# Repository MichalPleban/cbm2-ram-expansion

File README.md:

# CBM-II RAM expansion board

## Warning!

This project is obsolete. For a new hardware project, combining the 8088 card, memory expansion and other hardware features, see the repository at:

https://github.com/MichalPleban/cbm2-8088-ram-board

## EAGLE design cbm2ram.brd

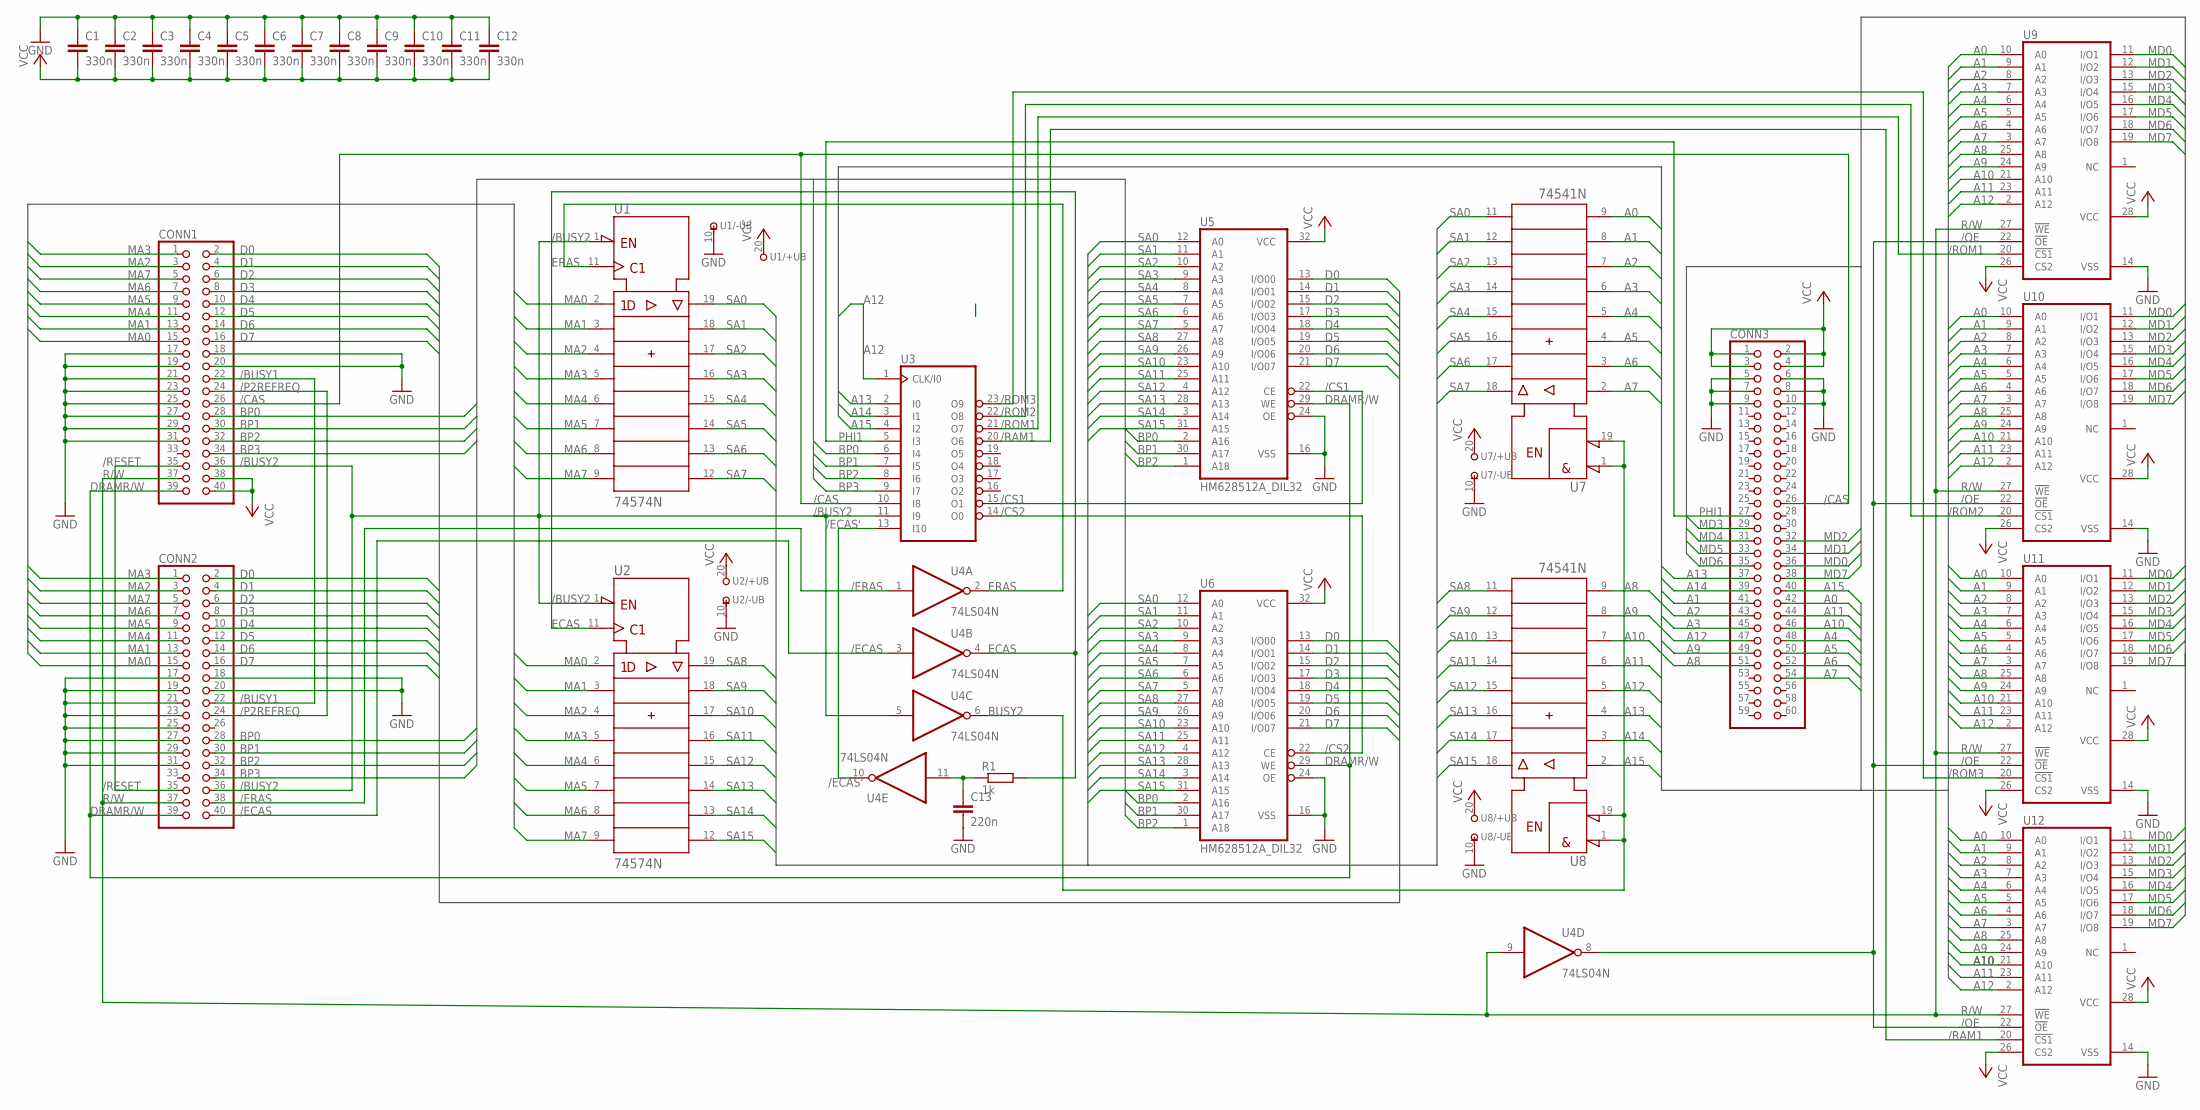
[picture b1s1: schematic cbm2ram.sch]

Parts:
C1, C2, C3, C4, C5, C6, C7, C8, C9, C10, C11, C12: 330n; C5B3
C13: 220n; C5B3
CONN1, CONN2: PINHD-2X20; 2X20
CONN3: PINHD-2X30; 2X30
R1: 1k; 0207/10
U1, U2: 74574N; DIL20
U3: 22V10; DIL24-3
U4: 74LS04N; DIL14
U5, U6: HM628512A_DIL32; DIL32
U7, U8: 74541N; DIL20
U9, U10, U11, U12: 6264A; DIL28-6

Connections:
/BUSY1: CONN1.22, CONN2.22
/BUSY2: CONN1.36, CONN2.36, U1.1 (!OC), U2.1 (!OC), U3.11 (I9), U4.5 (I)
/CAS: CONN1.26, CONN3.26, U3.10 (I8)
/CS1: U3.15 (O1), U5.22 (CE)
/CS2: U3.14 (O0), U6.22 (CE)
/ECAS: CONN2.40, U4.3 (I)
/ECAS': U3.13 (I10), U4.10 (O)
/ERAS: CONN2.38, U4.1 (I)
/OE: U4.8 (O), U9.22 (!OE), U10.22 (!OE), U11.22 (!OE), U12.22 (!OE)
/P2REFREQ: CONN1.24, CONN2.24
/RAM1: U3.20 (O6), U12.20 (!CS1)
/RESET: CONN1.35, CONN2.35
/ROM1: U3.21 (O7), U9.20 (!CS1)
/ROM2: U3.22 (O8), U10.20 (!CS1)
/ROM3: U3.23 (O9), U11.20 (!CS1)
A0: CONN3.42, U7.9 (A8), U9.10 (A0), U10.10 (A0), U11.10 (A0), U12.10 (A0)
A1: CONN3.41, U7.8 (A7), U9.9 (A1), U10.9 (A1), U11.9 (A1), U12.9 (A1)
A2: CONN3.43, U7.7 (A6), U9.8 (A2), U10.8 (A2), U11.8 (A2), U12.8 (A2)
A3: CONN3.45, U7.6 (A5), U9.7 (A3), U10.7 (A3), U11.7 (A3), U12.7 (A3)
A4: CONN3.48, U7.5 (A4), U9.6 (A4), U10.6 (A4), U11.6 (A4), U12.6 (A4)
A5: CONN3.50, U7.4 (A3), U9.5 (A5), U10.5 (A5), U11.5 (A5), U12.5 (A5)
A6: CONN3.52, U7.3 (A2), U9.4 (A6), U10.4 (A6), U11.4 (A6), U12.4 (A6)
A7: CONN3.54, U7.2 (A1), U9.3 (A7), U10.3 (A7), U11.3 (A7), U12.3 (A7)
A8: CONN3.51, U8.9 (A8), U9.25 (A8), U10.25 (A8), U11.25 (A8), U12.25 (A8)
A9: CONN3.49, U8.8 (A7), U9.24 (A9), U10.24 (A9), U11.24 (A9), U12.24 (A9)
A10: CONN3.46, U8.7 (A6), U9.21 (A10), U10.21 (A10), U11.21 (A10), U12.21 (A10)
A11: CONN3.44, U8.6 (A5), U9.23 (A11), U10.23 (A11), U11.23 (A11), U12.23 (A11)
A12: CONN3.47, U3.1 (CLK/I0), U8.5 (A4), U9.2 (A12), U10.2 (A12), U11.2 (A12), U12.2 (A12)
A13: CONN3.37, U3.2 (I0), U8.4 (A3)
A14: CONN3.39, U3.3 (I1), U8.3 (A2)
A15: CONN3.40, U3.4 (I2), U8.2 (A1)
BP0: CONN1.28, CONN2.28, U3.6 (I4), U5.2 (A16), U6.2 (A16)
BP1: CONN1.30, CONN2.30, U3.7 (I5), U5.30 (A17), U6.30 (A17)
BP2: CONN1.32, CONN2.32, U3.8 (I6), U5.1 (A18), U6.1 (A18)
BP3: CONN1.34, CONN2.34, U3.9 (I7)
BUSY2: U4.6 (O), U7.1 (!G1), U7.19 (!G2), U8.1 (!G1), U8.19 (!G2)
D0: CONN1.2, CONN2.2, U5.13 (I/O00), U6.13 (I/O00)
D1: CONN1.4, CONN2.4, U5.14 (I/O01), U6.14 (I/O01)
D2: CONN1.6, CONN2.6, U5.15 (I/O02), U6.15 (I/O02)
D3: CONN1.8, CONN2.8, U5.17 (I/O03), U6.17 (I/O03)
D4: CONN1.10, CONN2.10, U5.18 (I/O04), U6.18 (I/O04)
D5: CONN1.12, CONN2.12, U5.19 (I/O05), U6.19 (I/O05)
D6: CONN1.14, CONN2.14, U5.20 (I/O06), U6.20 (I/O06)
D7: CONN1.16, CONN2.16, U5.21 (I/O07), U6.21 (I/O07)
DRAMR/W: CONN1.39, CONN2.39, U5.29 (WE), U6.29 (WE)
ECAS: R1.2, U2.11 (CLK), U4.4 (O)
ECAS': C13.1, R1.1, U4.11 (I)
ERAS: U1.11 (CLK), U4.2 (O)
GND: C1.1, C2.1, C3.1, C4.1, C5.1, C6.1, C7.1, C8.1, C9.1, C10.1, C11.1, C12.1, C13.2, CONN1.17, CONN1.18, CONN1.19, CONN1.20, CONN1.21, CONN1.23, CONN1.25, CONN1.27, CONN1.29, CONN1.31, CONN2.17, CONN2.18, CONN2.19, CONN2.20, CONN2.21, CONN2.23, CONN2.25, CONN2.27, CONN2.29, CONN2.31, CONN3.5, CONN3.6, CONN3.7, CONN3.8, CONN3.9, CONN3.10, U1.10 (-UB), U2.10 (-UB), U3.12 (GND), U4.7 (GND), U5.16 (VSS), U5.24 (OE), U6.16 (VSS), U6.24 (OE), U7.10 (-UB), U8.10 (-UB), U9.14 (VSS), U10.14 (VSS), U11.14 (VSS), U12.14 (VSS)
MA0: CONN1.15, CONN2.15, U1.2 (1D), U2.2 (1D)
MA1: CONN1.13, CONN2.13, U1.3 (2D), U2.3 (2D)
MA2: CONN1.3, CONN2.3, U1.4 (3D), U2.4 (3D)
MA3: CONN1.1, CONN2.1, U1.5 (4D), U2.5 (4D)
MA4: CONN1.11, CONN2.11, U1.6 (5D), U2.6 (5D)
MA5: CONN1.9, CONN2.9, U1.7 (6D), U2.7 (6D)
MA6: CONN1.7, CONN2.7, U1.8 (7D), U2.8 (7D)
MA7: CONN1.5, CONN2.5, U1.9 (8D), U2.9 (8D)
MD0: CONN3.36, U9.11 (I/O1), U10.11 (I/O1), U11.11 (I/O1), U12.11 (I/O1)
MD1: CONN3.34, U9.12 (I/O2), U10.12 (I/O2), U11.12 (I/O2), U12.12 (I/O2)
MD2: CONN3.32, U9.13 (I/O3), U10.13 (I/O3), U11.13 (I/O3), U12.13 (I/O3)
MD3: CONN3.29, U9.15 (I/O4), U10.15 (I/O4), U11.15 (I/O4), U12.15 (I/O4)
MD4: CONN3.31, U9.16 (I/O5), U10.16 (I/O5), U11.16 (I/O5), U12.16 (I/O5)
MD5: CONN3.33, U9.17 (I/O6), U10.17 (I/O6), U11.17 (I/O6), U12.17 (I/O6)
MD6: CONN3.35, U9.18 (I/O7), U10.18 (I/O7), U11.18 (I/O7), U12.18 (I/O7)
MD7: CONN3.38, U9.19 (I/O8), U10.19 (I/O8), U11.19 (I/O8), U12.19 (I/O8)
PHI1: CONN3.27, U3.5 (I3)
R/W: CONN1.37, CONN2.37, U4.9 (I), U9.27 (!WE), U10.27 (!WE), U11.27 (!WE), U12.27 (!WE)
SA0: U1.19 (1Q), U5.12 (A0), U6.12 (A0), U7.11 (Y8)
SA1: U1.18 (2Q), U5.11 (A1), U6.11 (A1), U7.12 (Y7)
SA2: U1.17 (3Q), U5.10 (A2), U6.10 (A2), U7.13 (Y6)
SA3: U1.16 (4Q), U5.9 (A3), U6.9 (A3), U7.14 (Y5)
SA4: U1.15 (5Q), U5.8 (A4), U6.8 (A4), U7.15 (Y4)
SA5: U1.14 (6Q), U5.7 (A5), U6.7 (A5), U7.16 (Y3)
SA6: U1.13 (7Q), U5.6 (A6), U6.6 (A6), U7.17 (Y2)
SA7: U1.12 (8Q), U5.5 (A7), U6.5 (A7), U7.18 (Y1)
SA8: U2.19 (1Q), U5.27 (A8), U6.27 (A8), U8.11 (Y8)
SA9: U2.18 (2Q), U5.26 (A9), U6.26 (A9), U8.12 (Y7)
SA10: U2.17 (3Q), U5.23 (A10), U6.23 (A10), U8.13 (Y6)
SA11: U2.16 (4Q), U5.25 (A11), U6.25 (A11), U8.14 (Y5)
SA12: U2.15 (5Q), U5.4 (A12), U6.4 (A12), U8.15 (Y4)
SA13: U2.14 (6Q), U5.28 (A13), U6.28 (A13), U8.16 (Y3)
SA14: U2.13 (7Q), U5.3 (A14), U6.3 (A14), U8.17 (Y2)
SA15: U2.12 (8Q), U5.31 (A15), U6.31 (A15), U8.18 (Y1)
VCC: C1.2, C2.2, C3.2, C4.2, C5.2, C6.2, C7.2, C8.2, C9.2, C10.2, C11.2, C12.2, CONN1.38, CONN1.40, CONN3.1, CONN3.2, CONN3.3, CONN3.4, U1.20 (+UB), U2.20 (+UB), U3.24 (VCC), U4.14 (VCC), U5.32 (VCC), U6.32 (VCC), U7.20 (+UB), U8.20 (+UB), U9.26 (CS2), U9.28 (VCC), U10.26 (CS2), U10.28 (VCC), U11.26 (CS2), U11.28 (VCC), U12.26 (CS2), U12.28 (VCC)

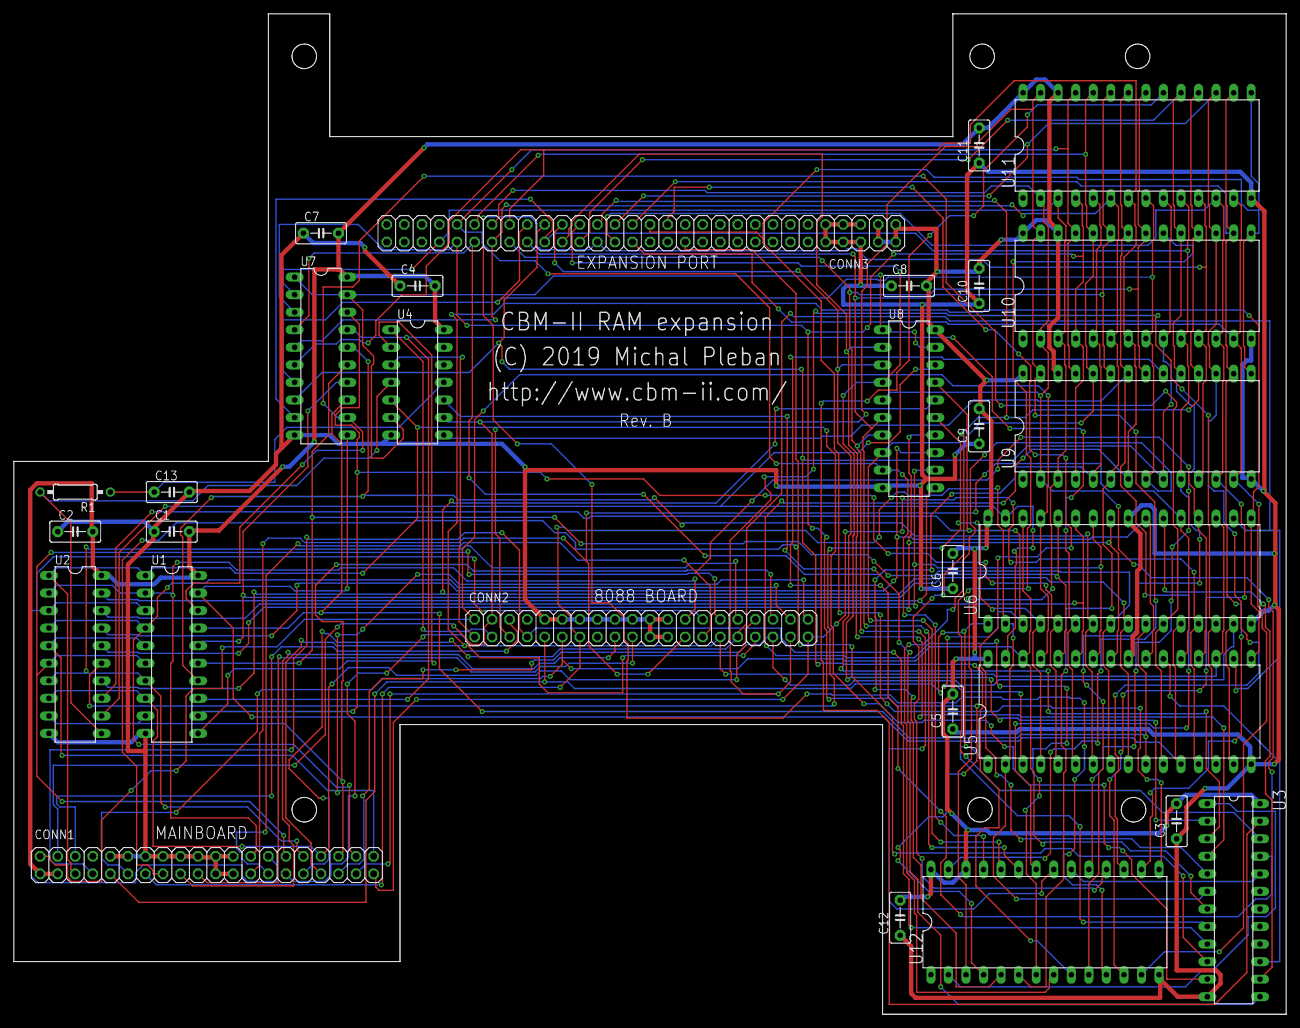
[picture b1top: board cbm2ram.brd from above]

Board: 2 copper layers, 184.1 x 144.8 mm, 29 parts (0 on the bottom side), 84 nets.

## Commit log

2018-04-17 Schematic of the 8088 processor interface
2018-05-13 Schematic of the 6509 interface
2018-12-16 Complete schematic
2018-12-16 Schematic corrections
2018-12-16 Firt autorouted board
2019-01-13 Added EPROM chips
2019-07-13 Complete board.
2019-08-04 JEDEC files for GAL22V10

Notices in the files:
cbm2ram.brd:
(C) 2019 Michal Pleban
